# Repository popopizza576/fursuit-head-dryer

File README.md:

# fursuit-head-dryer
A stand for your fursuit head that monitors humidity levels and dries your fursuit head. has space for maybe a scent pod or something, as well as silica gel packets

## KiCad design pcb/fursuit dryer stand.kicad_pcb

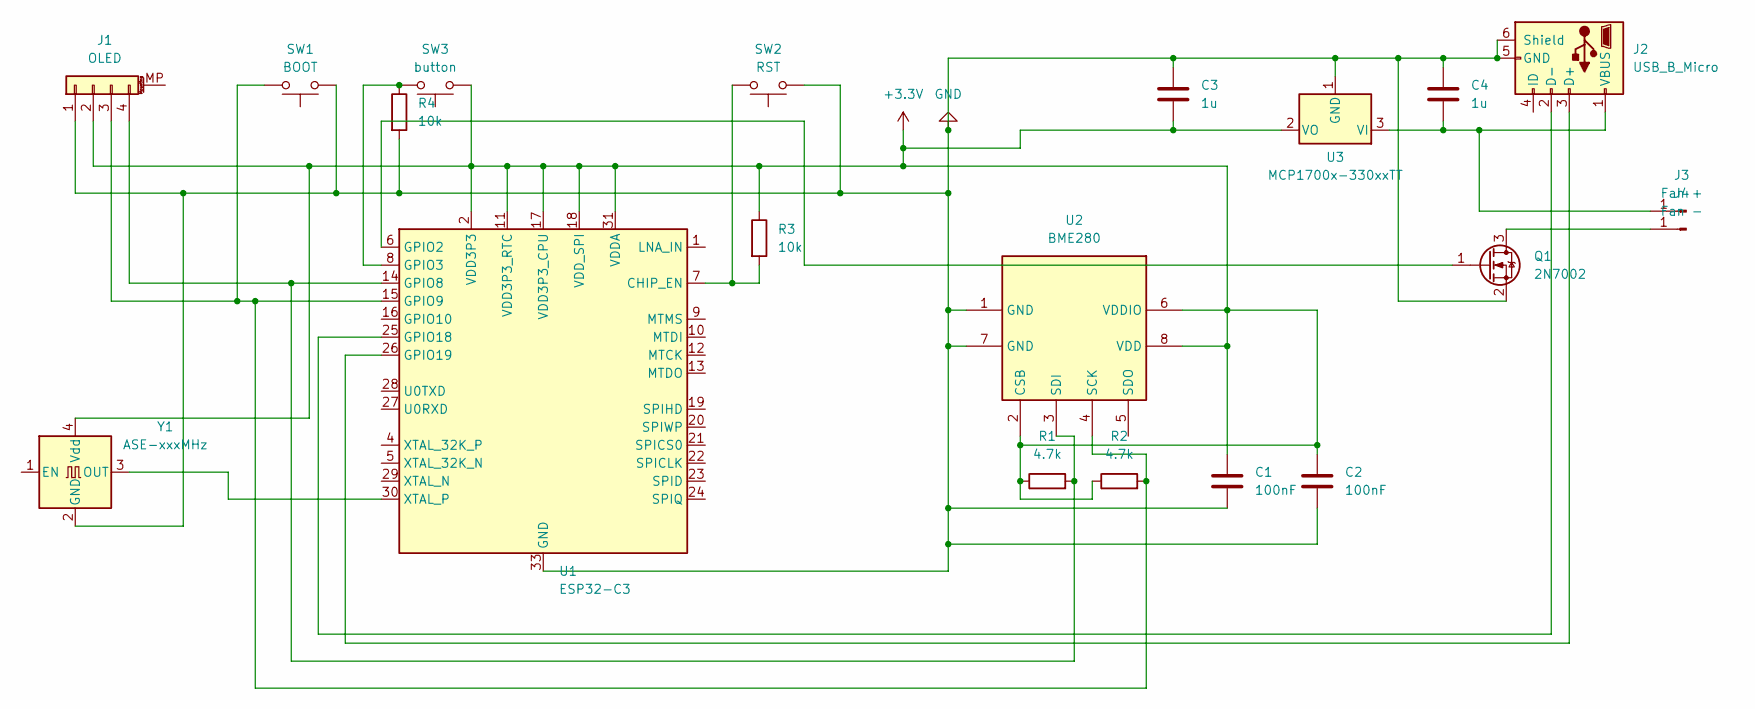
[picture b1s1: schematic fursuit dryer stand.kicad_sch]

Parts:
C1, C2: 100nF; C_0805_2012Metric_Pad1.18x1.45mm_HandSolder
C3, C4: 1u; C_0805_2012Metric_Pad1.18x1.45mm_HandSolder
J1: OLED; PinSocket_1x04_P2.54mm_Vertical_SMD_Pin1Left
J2: USB_B_Micro; USB_Micro-AB_Molex_47590-0001
J3: Fan +; SolderWirePad_1x01_SMD_1x2mm
J4: Fan -; SolderWirePad_1x01_SMD_1x2mm
Q1: 2N7002; SOT-23
R1, R2: 4.7k; R_0805_2012Metric_Pad1.20x1.40mm_HandSolder
R3, R4: 10k; R_0805_2012Metric_Pad1.20x1.40mm_HandSolder
SW1: BOOT; SW_SPST_CK_RS282G05A3
SW2: RST; SW_SPST_CK_RS282G05A3
SW3: button; SW_SPST_CK_RS282G05A3
U1: ESP32-C3; QFN-32-1EP_5x5mm_P0.5mm_EP3.7x3.7mm
U2: BME280; Bosch_LGA-8_2.5x2.5mm_P0.65mm_ClockwisePinNumbering
U3: MCP1700x-330xxTT; SOT-23
Y1: ASE-xxxMHz; Crystal_SMD_TXC_AX_8045-2Pin_8.0x4.5mm

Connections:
+3.3V: C1.1, C2.1, C3.2, J1.2, R1.1, R2.1, R3.1, SW3.1, U1.2 (VDD3P3), U1.3 (VDD3P3), U1.11 (VDD3P3_RTC), U1.17 (VDD3P3_CPU), U1.18 (VDD_SPI), U1.31 (VDDA), U1.32 (VDDA), U2.2 (CSB), U2.6 (VDDIO), U2.8 (VDD), U3.2 (VO), Y1.4 (Vdd)
GND: C1.2, C2.2, C3.1, C4.1, J1.1, J2.5 (GND), J2.6 (Shield), Q1.2 (S), R4.2, SW1.1, SW2.1, U1.33 (GND), U2.1 (GND), U2.7 (GND), U3.1 (GND), Y1.2 (GND)
unnamed: J1.3, R2.2, SW1.2, U1.15 (GPIO9), U2.4 (SCK)
unnamed: J1.4, R1.2, U1.14 (GPIO8), U2.3 (SDI)
unnamed: J2.3 (D+), U1.26 (GPIO19)
unnamed: J2.2 (D-), U1.25 (GPIO18)
unnamed: C4.2, J2.1 (VBUS), J3.1, U3.3 (VI)
unnamed: J4.1, Q1.3 (D)
unnamed: Q1.1 (G), U1.6 (GPIO2)
unnamed: R3.2, SW2.2, U1.7 (CHIP_EN)
unnamed: R4.1, SW3.2, U1.8 (GPIO3)
unnamed: U1.30 (XTAL_P), Y1.3 (OUT)

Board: 2 copper layers, 20 parts (18 on the bottom side), 12 nets, no tracks yet.

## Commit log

2026-05-28 Create idk
